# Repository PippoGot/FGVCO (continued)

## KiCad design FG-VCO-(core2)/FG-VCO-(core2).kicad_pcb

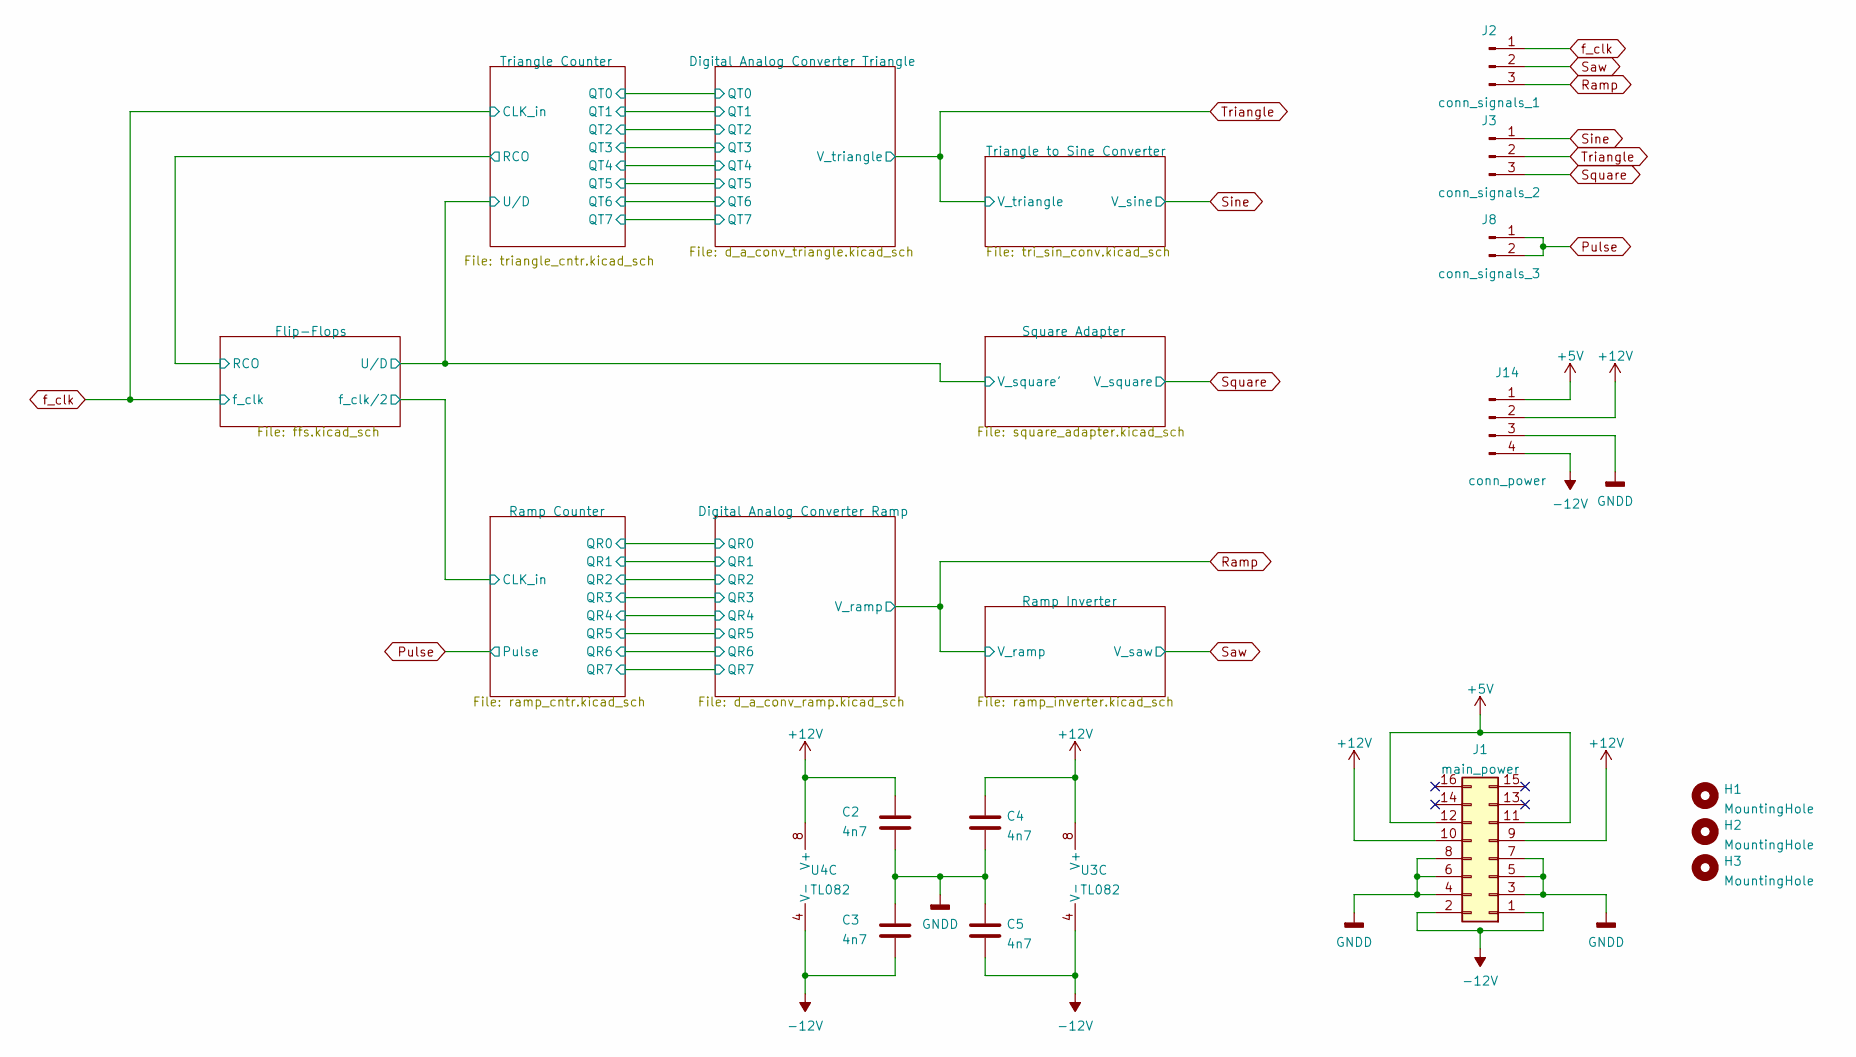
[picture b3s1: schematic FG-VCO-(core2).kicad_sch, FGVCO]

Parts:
C2, C3, C4, C5: 4n7; C_Disc_P2.54mm
H1, H2, H3: MountingHole; MountingHole_3.2mm_M3
J1: main_power; Eurorack custom eFuse board 2x08_P2.54mm
J2: conn_signals_1; PinHeader_1x03_P2.54mm_Vertical
J3: conn_signals_2; PinHeader_1x03_P2.54mm_Vertical
J8: conn_signals_3; PinHeader_1x02_P2.54mm_Vertical
J14: conn_power; PinHeader_1x04_P2.54mm_Vertical
U3, U4: TL082; DIP-8_central_caps

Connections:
+5V: J1.11, J1.12, J14.1; also elsewhere on the board
+12V: C2.1, C4.1, J1.9, J1.10, J14.2, U3.8 (V+), U4.8 (V+); also elsewhere on the board
-12V: C3.2, C5.2, J1.1, J1.2, J14.4, U3.4 (V-), U4.4 (V-); also elsewhere on the board
GNDD: C2.2, C3.1, C4.2, C5.1, J1.3, J1.4, J1.5, J1.6, J1.7, J1.8, J14.3; also elsewhere on the board
Pulse: J8.1, J8.2; also elsewhere on the board
Ramp: J2.3; also elsewhere on the board
Saw: J2.2; also elsewhere on the board
Sine: J3.1; also elsewhere on the board
Square: J3.3; also elsewhere on the board
Triangle: J3.2; also elsewhere on the board
f_clk: J2.1; also elsewhere on the board

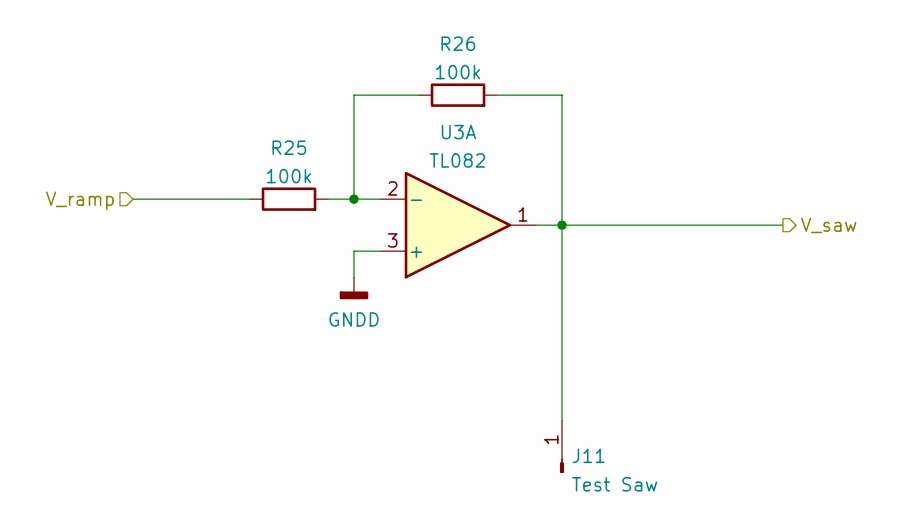
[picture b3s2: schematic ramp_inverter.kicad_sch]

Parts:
J11: Test Saw; PinHeader_1x01_P2.54mm_Vertical
R25, R26: 100k; R_Axial_DIN0207_L6.3mm_D2.5mm_P10.16mm_Horizontal
U3: TL082; DIP-8_central_caps

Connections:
GNDD: U3.3 (+); also elsewhere on the board
unnamed: R25.2, R26.1, U3.2 (-)
Ramp: R25.1; also elsewhere on the board
Saw: J11.1, R26.2, U3.1; also elsewhere on the board

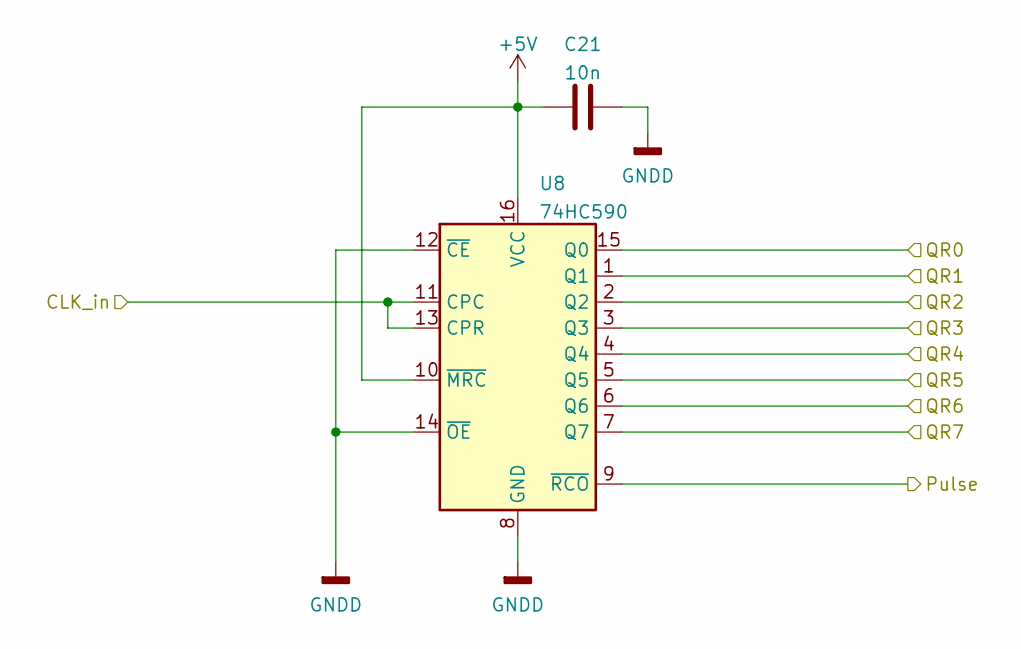
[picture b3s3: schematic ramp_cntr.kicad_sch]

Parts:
C21: 10n; C_Disc_P2.54mm
U8: 74HC590; DIP-16_central_caps

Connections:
+5V: C21.2, U8.10 (~MRC), U8.16 (VCC); also elsewhere on the board
/Digital Analog Converter Ramp/QR0: U8.15 (Q0); also elsewhere on the board
/Digital Analog Converter Ramp/QR1: U8.1 (Q1); also elsewhere on the board
/Digital Analog Converter Ramp/QR2: U8.2 (Q2); also elsewhere on the board
/Digital Analog Converter Ramp/QR3: U8.3 (Q3); also elsewhere on the board
/Digital Analog Converter Ramp/QR4: U8.4 (Q4); also elsewhere on the board
/Digital Analog Converter Ramp/QR5: U8.5 (Q5); also elsewhere on the board
/Digital Analog Converter Ramp/QR6: U8.6 (Q6); also elsewhere on the board
/Digital Analog Converter Ramp/QR7: U8.7 (Q7); also elsewhere on the board
/Flip-Flops/f_clk/2: U8.11 (CPC), U8.13 (CPR); also elsewhere on the board
GNDD: C21.1, U8.8 (GND), U8.12 (~CE), U8.14 (~OE); also elsewhere on the board
Pulse: U8.9 (~RCO); also elsewhere on the board

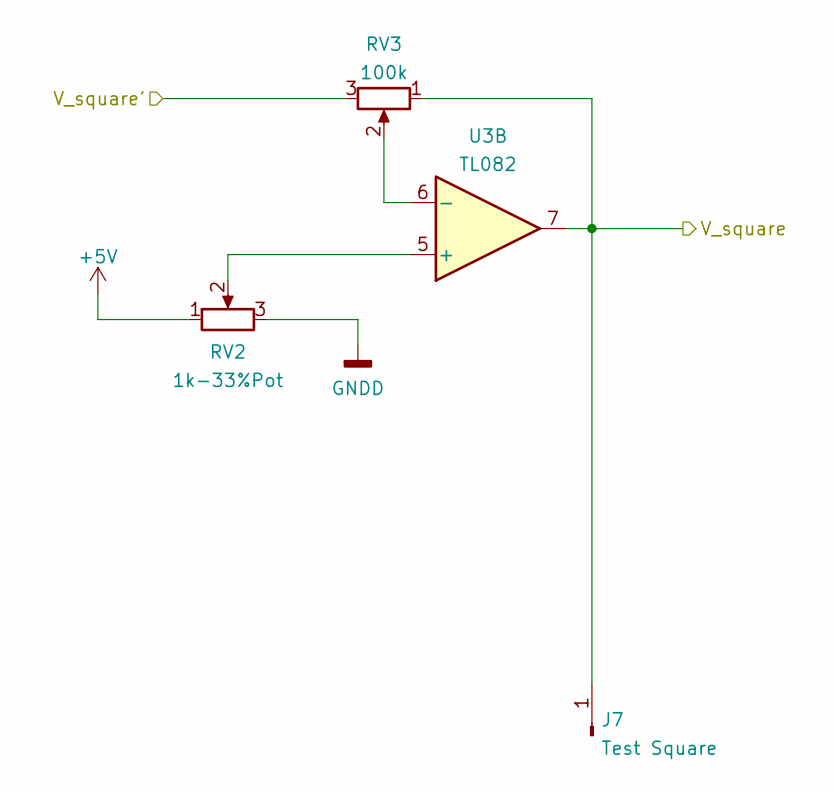
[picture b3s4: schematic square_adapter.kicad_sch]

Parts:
J7: Test Square; PinHeader_1x01_P2.54mm_Vertical
RV2: 1k-33%Pot; Potentiometer_Vishay_T73YP_Vertical
RV3: 100k; Potentiometer_Vishay_T73YP_Vertical
U3: TL082; DIP-8_central_caps

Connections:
+5V: RV2.1; also elsewhere on the board
/Flip-Flops/U/D: RV3.3; also elsewhere on the board
GNDD: RV2.3; also elsewhere on the board
unnamed: RV2.2, U3.5 (+)
unnamed: RV3.2, U3.6 (-)
Square: J7.1, RV3.1, U3.7; also elsewhere on the board

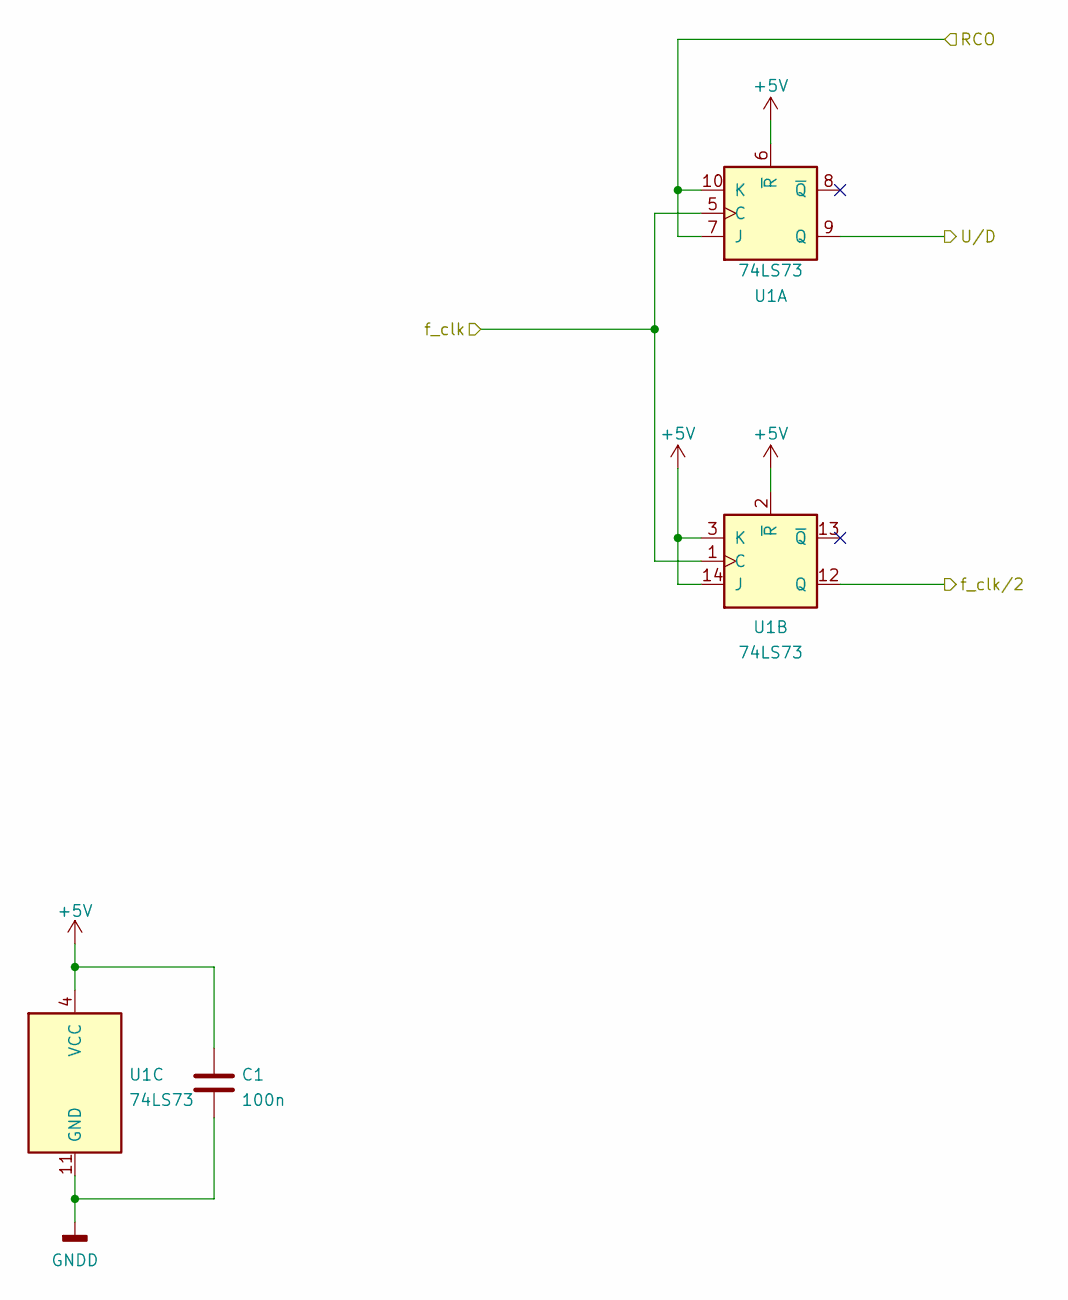
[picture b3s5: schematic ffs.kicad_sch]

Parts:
C1: 100n; C_Disc_P2.54mm
U1: 74LS73; DIP-14_central_caps

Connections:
+5V: C1.1, U1.2 (~R), U1.3 (K), U1.4 (VCC), U1.6 (~R), U1.14 (J); also elsewhere on the board
/Flip-Flops/RCO: U1.7 (J), U1.10 (K); also elsewhere on the board
/Flip-Flops/U/D: U1.9 (Q); also elsewhere on the board
/Flip-Flops/f_clk/2: U1.12 (Q); also elsewhere on the board
GNDD: C1.2, U1.11 (GND); also elsewhere on the board
f_clk: U1.1 (C), U1.5 (C); also elsewhere on the board

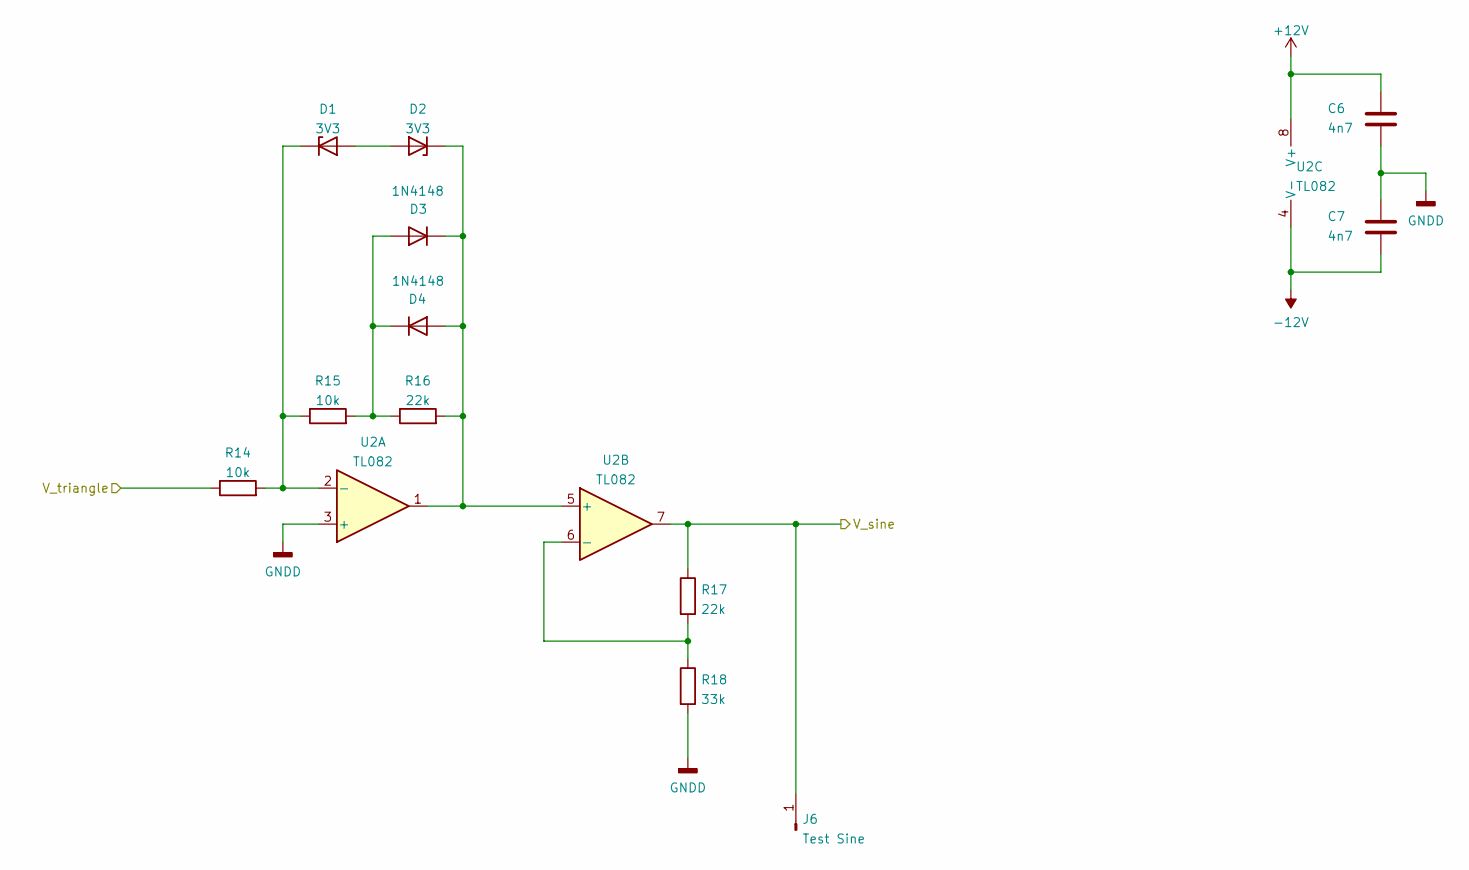
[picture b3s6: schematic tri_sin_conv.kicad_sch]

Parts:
C6, C7: 4n7; C_Disc_P2.54mm
D1, D2: 3V3; D_DO-35_SOD27_P7.62mm_Horizontal
D3, D4: 1N4148; D_DO-35_SOD27_P7.62mm_Horizontal
J6: Test Sine; PinHeader_1x01_P2.54mm_Vertical
R14, R15: 10k; R_Axial_DIN0207_L6.3mm_D2.5mm_P10.16mm_Horizontal
R16, R17: 22k; R_Axial_DIN0207_L6.3mm_D2.5mm_P10.16mm_Horizontal
R18: 33k; R_Axial_DIN0207_L6.3mm_D2.5mm_P10.16mm_Horizontal
U2: TL082; DIP-8_central_caps

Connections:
+12V: C6.1, U2.8 (V+); also elsewhere on the board
-12V: C7.2, U2.4 (V-); also elsewhere on the board
GNDD: C6.2, C7.1, R18.2, U2.3 (+); also elsewhere on the board
unnamed: D1.1 (K), R14.2, R15.1, U2.2 (-)
unnamed: D1.2 (A), D2.2 (A)
unnamed: D2.1 (K), D3.1 (K), D4.2 (A), R16.2, U2.1, U2.5 (+)
unnamed: D3.2 (A), D4.1 (K), R15.2, R16.1
unnamed: R17.2, R18.1, U2.6 (-)
Sine: J6.1, R17.1, U2.7; also elsewhere on the board
Triangle: R14.1; also elsewhere on the board

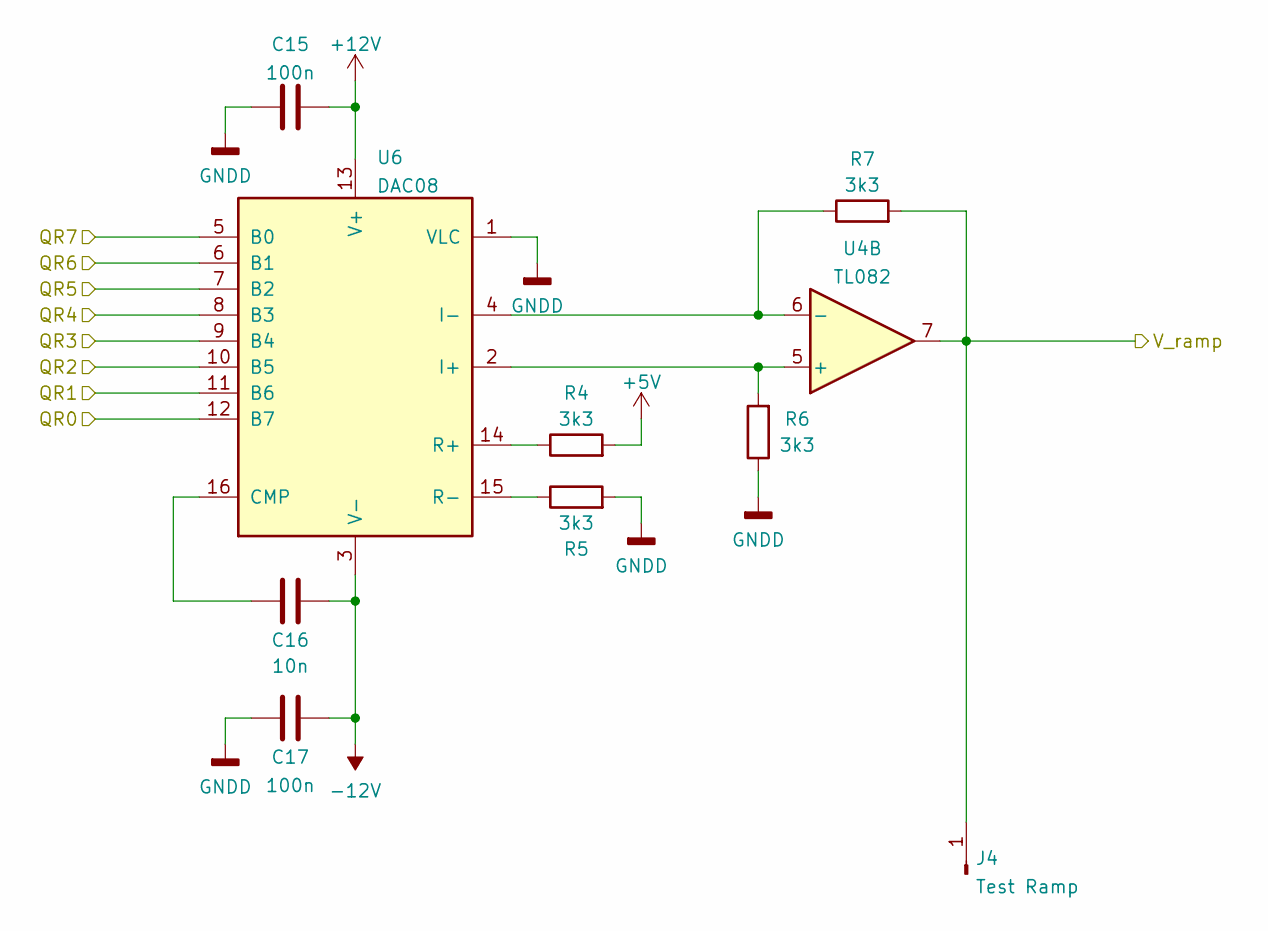
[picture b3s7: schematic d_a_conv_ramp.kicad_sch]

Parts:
C15, C17: 100n; C_Disc_P2.54mm
C16: 10n; C_Disc_P2.54mm
J4: Test Ramp; PinHeader_1x01_P2.54mm_Vertical
R4, R5, R6, R7: 3k3; R_Axial_DIN0207_L6.3mm_D2.5mm_P10.16mm_Horizontal
U4: TL082; DIP-8_central_caps
U6: DAC08; DIP-16_central_caps

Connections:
+5V: R4.2; also elsewhere on the board
+12V: C15.2, U6.13 (V+); also elsewhere on the board
-12V: C16.1, C17.1, U6.3 (V-); also elsewhere on the board
/Digital Analog Converter Ramp/QR0: U6.12 (B7); also elsewhere on the board
/Digital Analog Converter Ramp/QR1: U6.11 (B6); also elsewhere on the board
/Digital Analog Converter Ramp/QR2: U6.10 (B5); also elsewhere on the board
/Digital Analog Converter Ramp/QR3: U6.9 (B4); also elsewhere on the board
/Digital Analog Converter Ramp/QR4: U6.8 (B3); also elsewhere on the board
/Digital Analog Converter Ramp/QR5: U6.7 (B2); also elsewhere on the board
/Digital Analog Converter Ramp/QR6: U6.6 (B1); also elsewhere on the board
/Digital Analog Converter Ramp/QR7: U6.5 (B0); also elsewhere on the board
GNDD: C15.1, C17.2, R5.2, R6.1, U6.1 (VLC); also elsewhere on the board
unnamed: C16.2, U6.16 (CMP)
unnamed: R4.1, U6.14 (R+)
unnamed: R5.1, U6.15 (R-)
unnamed: R6.2, U4.5 (+), U6.2 (I+)
unnamed: R7.1, U4.6 (-), U6.4 (I-)
Ramp: J4.1, R7.2, U4.7; also elsewhere on the board

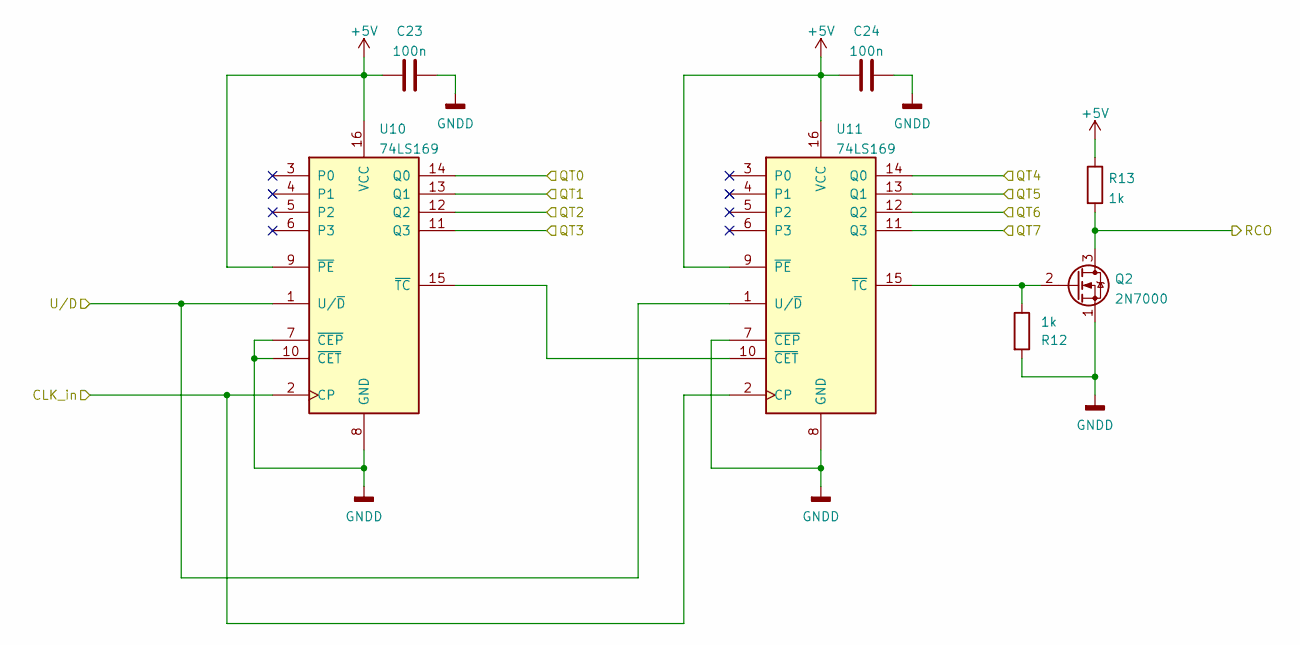
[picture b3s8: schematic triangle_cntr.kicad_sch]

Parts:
C23, C24: 100n; C_Disc_P2.54mm
Q2: 2N7000; TO-92
R12, R13: 1k; R_Axial_DIN0207_L6.3mm_D2.5mm_P10.16mm_Horizontal
U10, U11: 74LS169; DIP-16_central_caps

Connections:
+5V: C23.1, C24.1, R13.1, U10.9 (~PE), U10.16 (VCC), U11.9 (~PE), U11.16 (VCC); also elsewhere on the board
/Digital Analog Converter Triangle/QT0: U10.14 (Q0); also elsewhere on the board
/Digital Analog Converter Triangle/QT1: U10.13 (Q1); also elsewhere on the board
/Digital Analog Converter Triangle/QT2: U10.12 (Q2); also elsewhere on the board
/Digital Analog Converter Triangle/QT3: U10.11 (Q3); also elsewhere on the board
/Digital Analog Converter Triangle/QT4: U11.14 (Q0); also elsewhere on the board
/Digital Analog Converter Triangle/QT5: U11.13 (Q1); also elsewhere on the board
/Digital Analog Converter Triangle/QT6: U11.12 (Q2); also elsewhere on the board
/Digital Analog Converter Triangle/QT7: U11.11 (Q3); also elsewhere on the board
/Flip-Flops/RCO: Q2.3 (D), R13.2; also elsewhere on the board
/Flip-Flops/U/D: U10.1 (U/~D), U11.1 (U/~D); also elsewhere on the board
GNDD: C23.2, C24.2, Q2.1 (S), R12.2, U10.7 (~CEP), U10.8 (GND), U10.10 (~CET), U11.7 (~CEP), U11.8 (GND); also elsewhere on the board
unnamed: Q2.2 (G), R12.1, U11.15 (~TC)
unnamed: U10.15 (~TC), U11.10 (~CET)
f_clk: U10.2 (CP), U11.2 (CP); also elsewhere on the board

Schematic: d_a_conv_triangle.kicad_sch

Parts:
C18, C20: 100n; C_Disc_P2.54mm
C19: 10n; C_Disc_P2.54mm
J5: Test Triangle; PinHeader_1x01_P2.54mm_Vertical
R8, R9, R10, R11: 3k3; R_Axial_DIN0207_L6.3mm_D2.5mm_P10.16mm_Horizontal
U4: TL082; DIP-8_central_caps
U7: DAC08; DIP-16_central_caps

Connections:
+5V: R8.1; also elsewhere on the board
+12V: C18.2, U7.13 (V+); also elsewhere on the board
-12V: C19.1, C20.1, U7.3 (V-); also elsewhere on the board
/Digital Analog Converter Triangle/QT0: U7.12 (B7); also elsewhere on the board
/Digital Analog Converter Triangle/QT1: U7.11 (B6); also elsewhere on the board
/Digital Analog Converter Triangle/QT2: U7.10 (B5); also elsewhere on the board
/Digital Analog Converter Triangle/QT3: U7.9 (B4); also elsewhere on the board
/Digital Analog Converter Triangle/QT4: U7.8 (B3); also elsewhere on the board
/Digital Analog Converter Triangle/QT5: U7.7 (B2); also elsewhere on the board
/Digital Analog Converter Triangle/QT6: U7.6 (B1); also elsewhere on the board
/Digital Analog Converter Triangle/QT7: U7.5 (B0); also elsewhere on the board
GNDD: C18.1, C20.2, R9.2, R10.1, U7.1 (VLC); also elsewhere on the board
unnamed: C19.2, U7.16 (CMP)
unnamed: R8.2, U7.14 (R+)
unnamed: R9.1, U7.15 (R-)
unnamed: R10.2, U4.3 (+), U7.2 (I+)
unnamed: R11.1, U4.2 (-), U7.4 (I-)
Triangle: J5.1, R11.2, U4.1; also elsewhere on the board

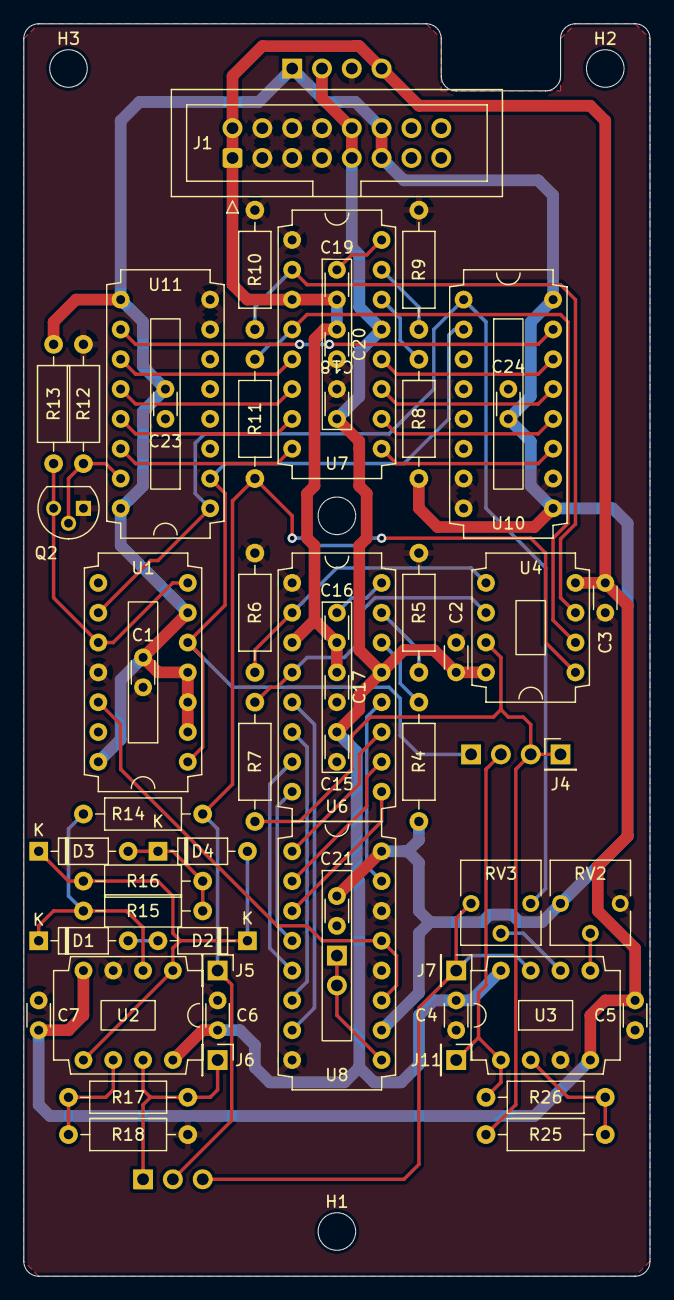
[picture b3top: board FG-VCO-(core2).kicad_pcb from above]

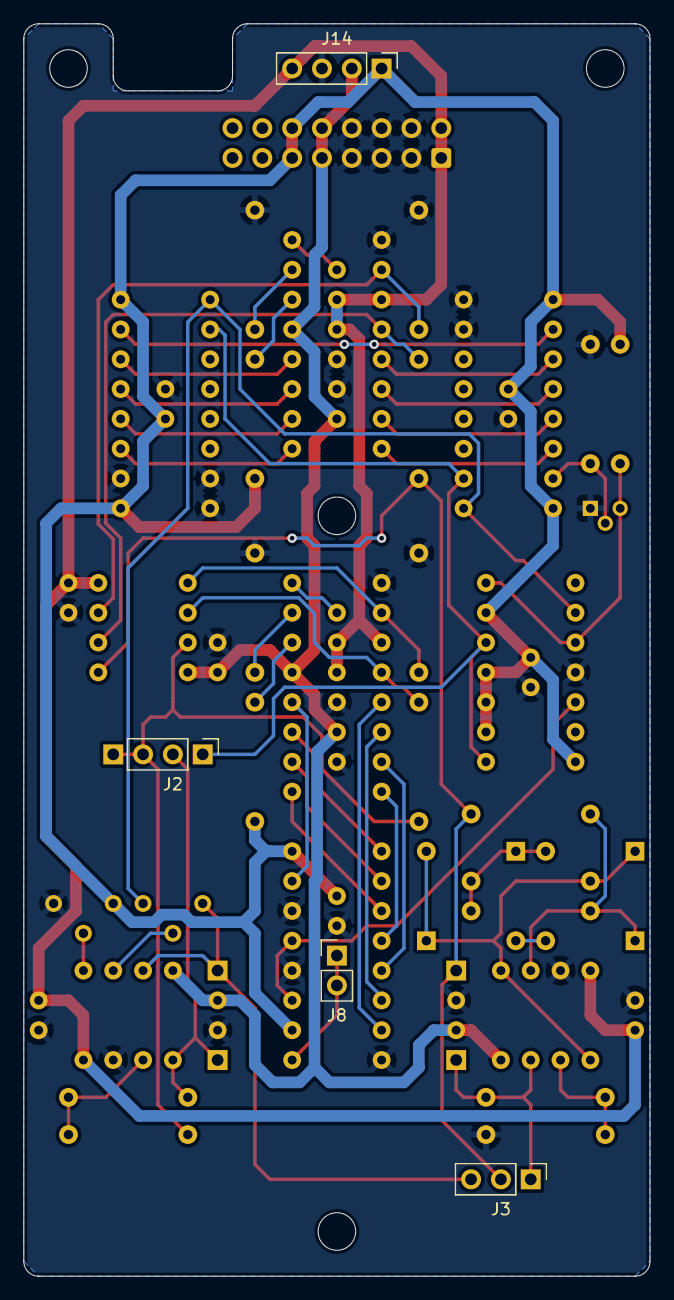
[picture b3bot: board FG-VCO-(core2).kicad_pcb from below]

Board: 2 copper layers, 53.3 x 106.7 mm, 62 parts (4 on the bottom side), 50 nets.

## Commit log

2022-08-03 init
2022-08-03 ch2 refining
2022-08-03 deleted template folder
2022-08-05 revisione capitoli, aggiornamento immagini e acquisizioni
2022-08-09 generated gerbers, added plots and table in ch2
2022-08-09 same as previous, for the whole folder
2022-08-12 first revision
2022-08-12 bibliography fail
2022-08-19 table snippets and started ch4
2022-08-26 refined to chapter 4
2022-08-28 finished ch06 and added appendix
2022-09-07 finished ch5 and 6, added figures
2022-09-09 finished writing, on to revision
2022-09-12 completed
